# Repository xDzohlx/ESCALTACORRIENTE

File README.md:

# ESCALTACORRIENTE
Driver para motor de alta corriente

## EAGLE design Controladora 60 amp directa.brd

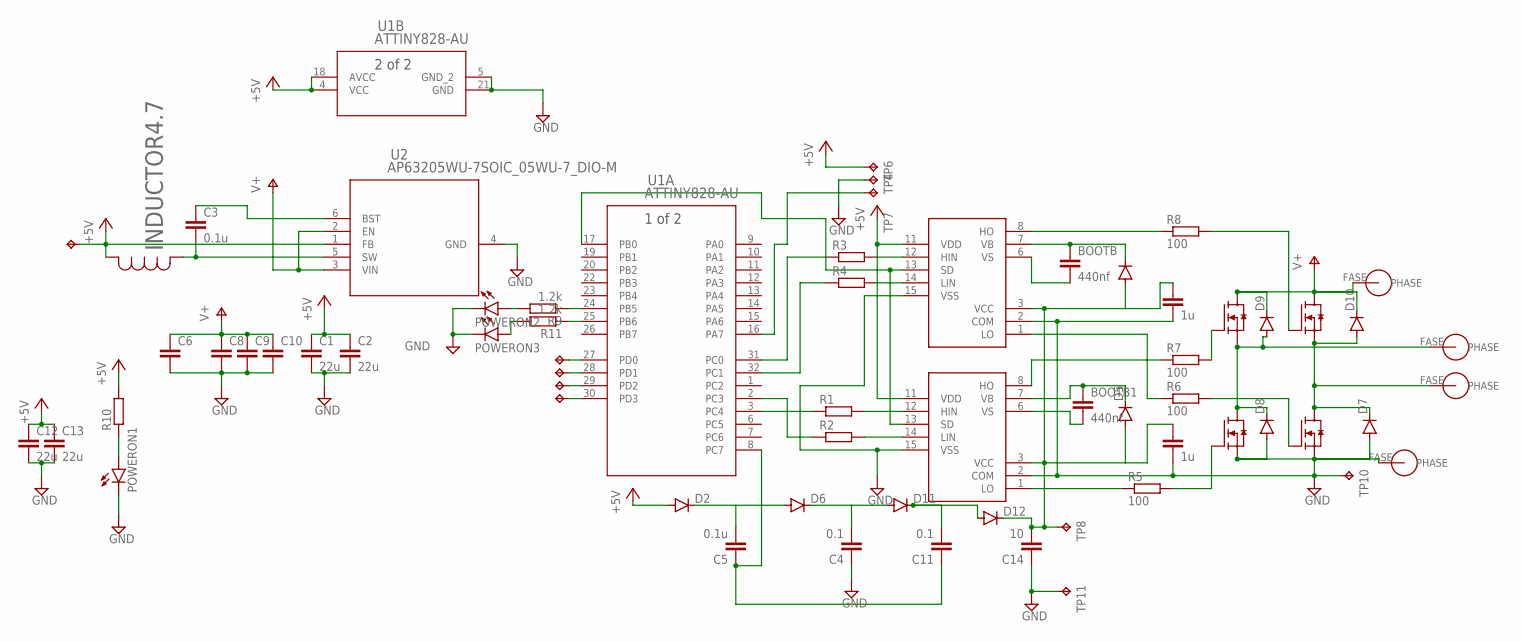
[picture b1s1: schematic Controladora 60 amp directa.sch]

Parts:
BOOTB, BOOTB1: 440nf; C0805
BYPASSBOOT, BYPASSBOOT2: 1u; C0805
C1, C2: 22u; C0805
C3: 0.1u; C0402
C4, C11: 0.1; C0805
C5: 0.1u; C0805
C6, C8: C-EUC0805; C0805
C9, C10: C-EU050-035X075; C050-035X075
C12, C13: 22u; C0402
C14: 10; C0805
D1, D3: IRS2110SPBF; SOIC127P1030X265-16N
D2, D4, D5, D6, D7, D8, D9, D10, D11, D12: DIODE-MINIMELF; MINIMELF
FASEA, FASEA1, FASEA2, FASEA3: PHASE; POWEROUT
LA, LA1, LA2, LA3: IPB180N06S4-H1; PG-TO263-7-3
POWERON1, POWERON2, POWERON3: LEDCHIPLED_0603; CHIPLED_0603
R1, R2, R3, R4, R10: R-EU_M0805; M0805
R5, R6, R7, R8: 100; M0805
R9, R11: 1.2k; M0805
TP1, TP2, TP3, TP4, TP5, TP6, TP7: TPTP16SQ; TP16SQ
TP8, TP9, TP10, TP11: TPB1,27; B1,27
U1: ATTINY828-AU; 32A_ATM
U2: AP63205WU-7SOIC_05WU-7_DIO-M; SOIC_05WU-7_DIO-M
U$1: INDUCTOR4.7; IND_NRS5030T100MMGJ_TAY

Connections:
+5V: C1.1, C2.1, C12.1, C13.1, D1.11 (VDD), D2.A, D3.11 (VDD), R10.2, TP6.TP, TP9.TP, U1.4 (VCC), U1.18 (AVCC), U2.1 (FB), U$1.1
GND: BYPASSBOOT.2, BYPASSBOOT2.2, C1.2, C2.2, C4.1, C6.2, C8.2, C9.2, C10.2, C12.2, C13.2, C14.1, D1.2 (COM), D1.15 (VSS), D3.2 (COM), D3.15 (VSS), D7.A, D8.A, FASEA3.FASE, LA1.2 (S), LA1.3 (S), LA1.5 (S), LA1.6 (S), LA1.7 (S), LA3.2 (S), LA3.3 (S), LA3.5 (S), LA3.6 (S), LA3.7 (S), POWERON1.C, POWERON2.C, POWERON3.C, TP4.TP, TP10.TP, TP11.TP, U1.5 (GND_2), U1.21 (GND), U2.4 (GND)
unnamed: TP3.TP, U1.30 (PD3)
unnamed: TP2.TP, U1.29 (PD2)
unnamed: TP1.TP, U1.28 (PD1)
unnamed: TP5.TP, U1.27 (PD0)
unnamed: R1.1, U1.3 (PC4)
unnamed: R2.1, U1.2 (PC3)
unnamed: BYPASSBOOT.1, BYPASSBOOT2.1, C14.2, D1.3 (VCC), D3.3 (VCC), D4.A, D5.A, D12.C, TP8.TP
unnamed: C5.2, D2.C, D6.A
unnamed: D1.12 (HIN), R1.2
unnamed: D1.14 (LIN), R2.2
unnamed: R3.1, U1.31 (PC0)
unnamed: D3.12 (HIN), R3.2
unnamed: R4.1, U1.32 (PC1)
unnamed: D3.14 (LIN), R4.2
unnamed: C3.2, U2.5 (SW), U$1.2
unnamed: TP7.TP, U1.16 (PA7)
unnamed: D1.13 (SD), D3.13 (SD), U1.17 (PB0)
unnamed: D8.C, D9.A, FASEA.FASE, LA.2 (S), LA.3 (S), LA.5 (S), LA.6 (S), LA.7 (S), LA1.8 (D)
unnamed: D7.C, D10.A, FASEA1.FASE, LA2.2 (S), LA2.3 (S), LA2.5 (S), LA2.6 (S), LA2.7 (S), LA3.8 (D)
unnamed: C5.1, C11.1, U1.8 (PC7)
unnamed: D1.1 (LO), R5.1
unnamed: C3.1, U2.6 (BST)
unnamed: LA3.1 (G), R6.2
unnamed: D3.1 (LO), R6.1
unnamed: LA1.1 (G), R5.2
unnamed: D1.8 (HO), R7.1
unnamed: LA2.1 (G), R8.2
unnamed: D3.8 (HO), R8.1
unnamed: LA.1 (G), R7.2
unnamed: BOOTB1.1, D1.7 (VB), D5.C
unnamed: BOOTB1.2, D1.6 (VS)
unnamed: BOOTB.1, D3.7 (VB), D4.C
unnamed: BOOTB.2, D3.6 (VS)
unnamed: R9.1, U1.24 (PB5)
unnamed: POWERON1.A, R10.1
unnamed: POWERON2.A, R9.2
unnamed: R11.1, U1.25 (PB6)
unnamed: POWERON3.A, R11.2
unnamed: C4.2, D6.C, D11.A
unnamed: C11.2, D11.C, D12.A
V+: C6.1, C8.1, C9.1, C10.1, D9.C, D10.C, FASEA2.FASE, LA.8 (D), LA2.8 (D), U2.2 (EN), U2.3 (VIN)

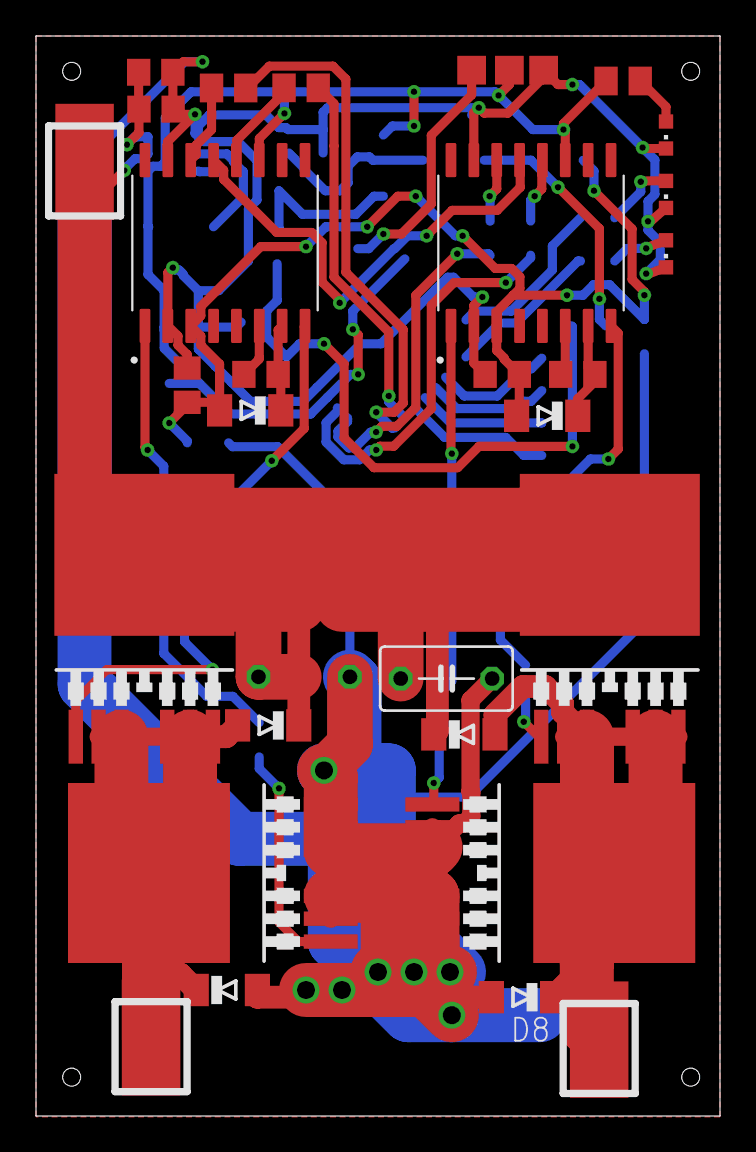
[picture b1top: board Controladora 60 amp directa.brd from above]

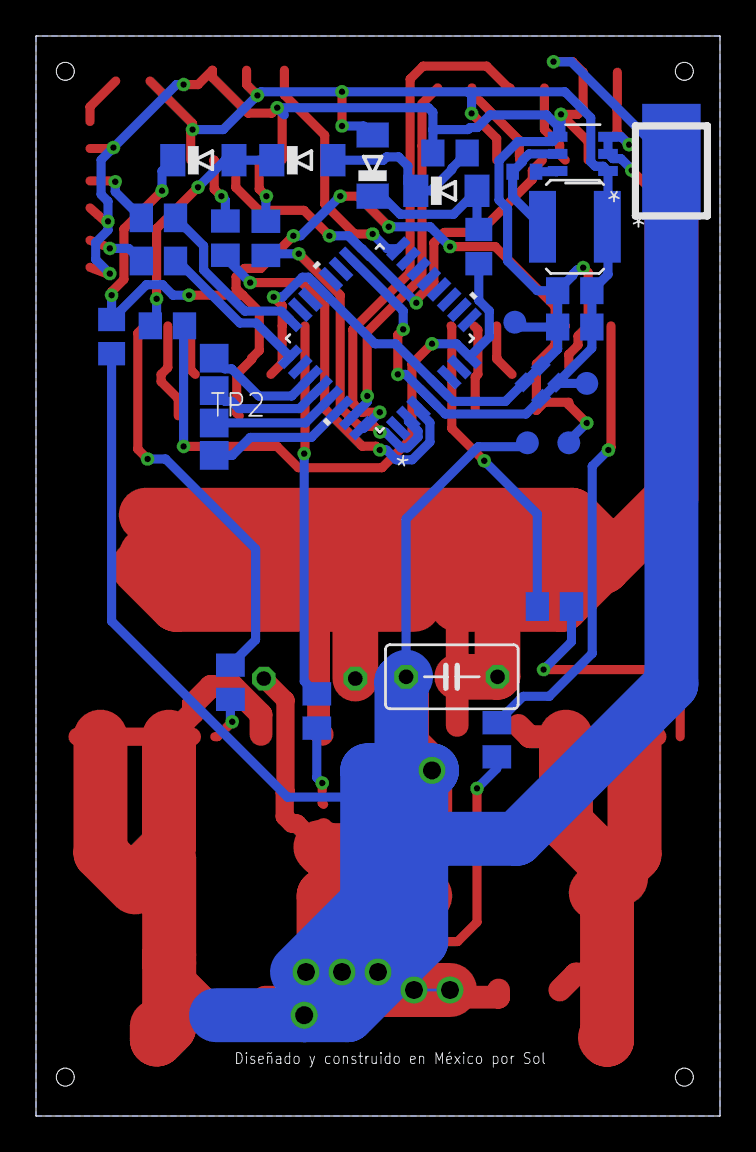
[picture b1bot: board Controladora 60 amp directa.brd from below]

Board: 2 copper layers, 38.0 x 60.0 mm, 65 parts (34 on the bottom side), 43 nets.

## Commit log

2020-08-04 Create LICENSE

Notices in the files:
parts and their libraries:
COPYRIGHT: Copyright (C) 2018 Accelerated Designs. All rights reserved
